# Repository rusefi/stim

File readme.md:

[Interactive Pinout](https://rusefi.com/docs/pinouts/stim/)

## User Manual

* 12v DC power required
* one microUSB cable required for operation
* sometimes second microUSB is useful for firmware update

* [Download Putty](https://www.chiark.greenend.org.uk/~sgtatham/putty/latest.html)
* bottom microUSB is required for operation
* top microUSB is sometimes needed for firmware updates
* blinking blue LD2 means "alive"
* red LD3 means "board has failed test
* green LD1 next to blinking blue means "test successful"

See https://github.com/rusefi/rusefi-hardware/tree/main/digital-inputs for firmware

Part of https://github.com/rusefi/rusefi infrastucture

https://github.com/rusefi/rusefi/wiki/dev-hardware-quality-control

# Digital Inputs
- 48 channels of high/low digital inputs
- pin requirment: 4 ADC inputs and 9 GPIO

GPIO:
* output: x4 address pins
* output: x4 test control pins
* output: mux off

See https://github.com/rusefi/stim/issues/6

# Changelog

## rev C

* CAN board fix
* second CAN board added
* OUT0 pin moved from PA11 to PD8
* https://github.com/rusefi/stim/issues?q=label%3Arev-C+is%3Aclosed

## rev 0.2

* CAN bus
* superseal header

##  rev 0.1
* it works!

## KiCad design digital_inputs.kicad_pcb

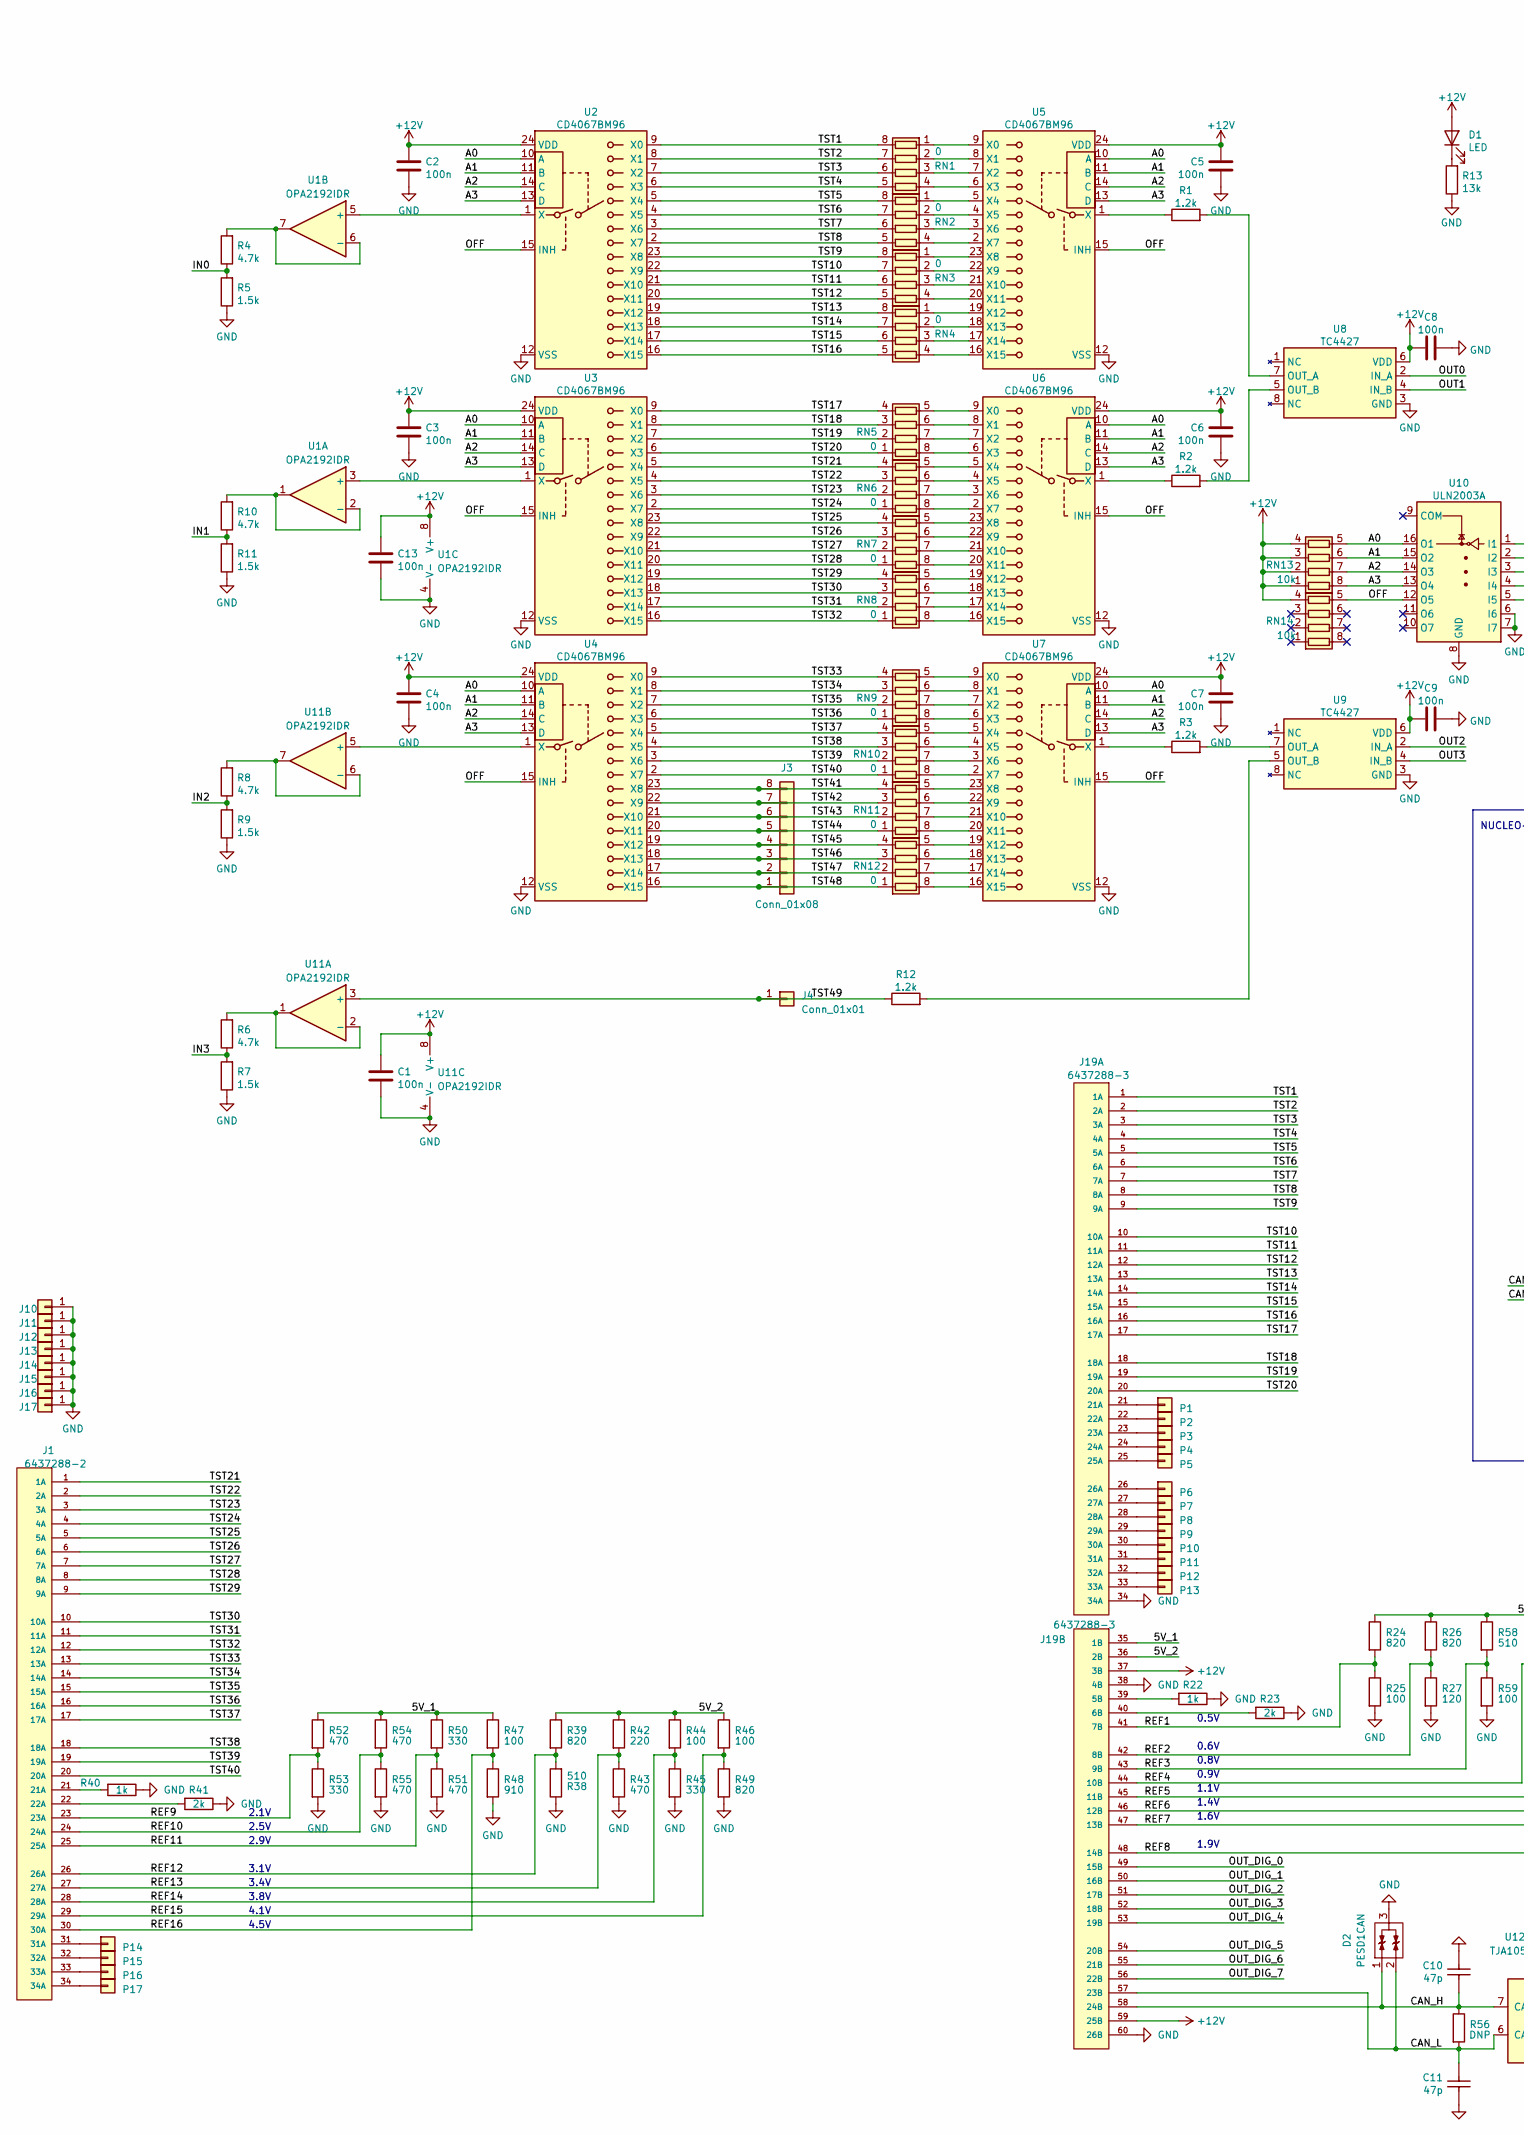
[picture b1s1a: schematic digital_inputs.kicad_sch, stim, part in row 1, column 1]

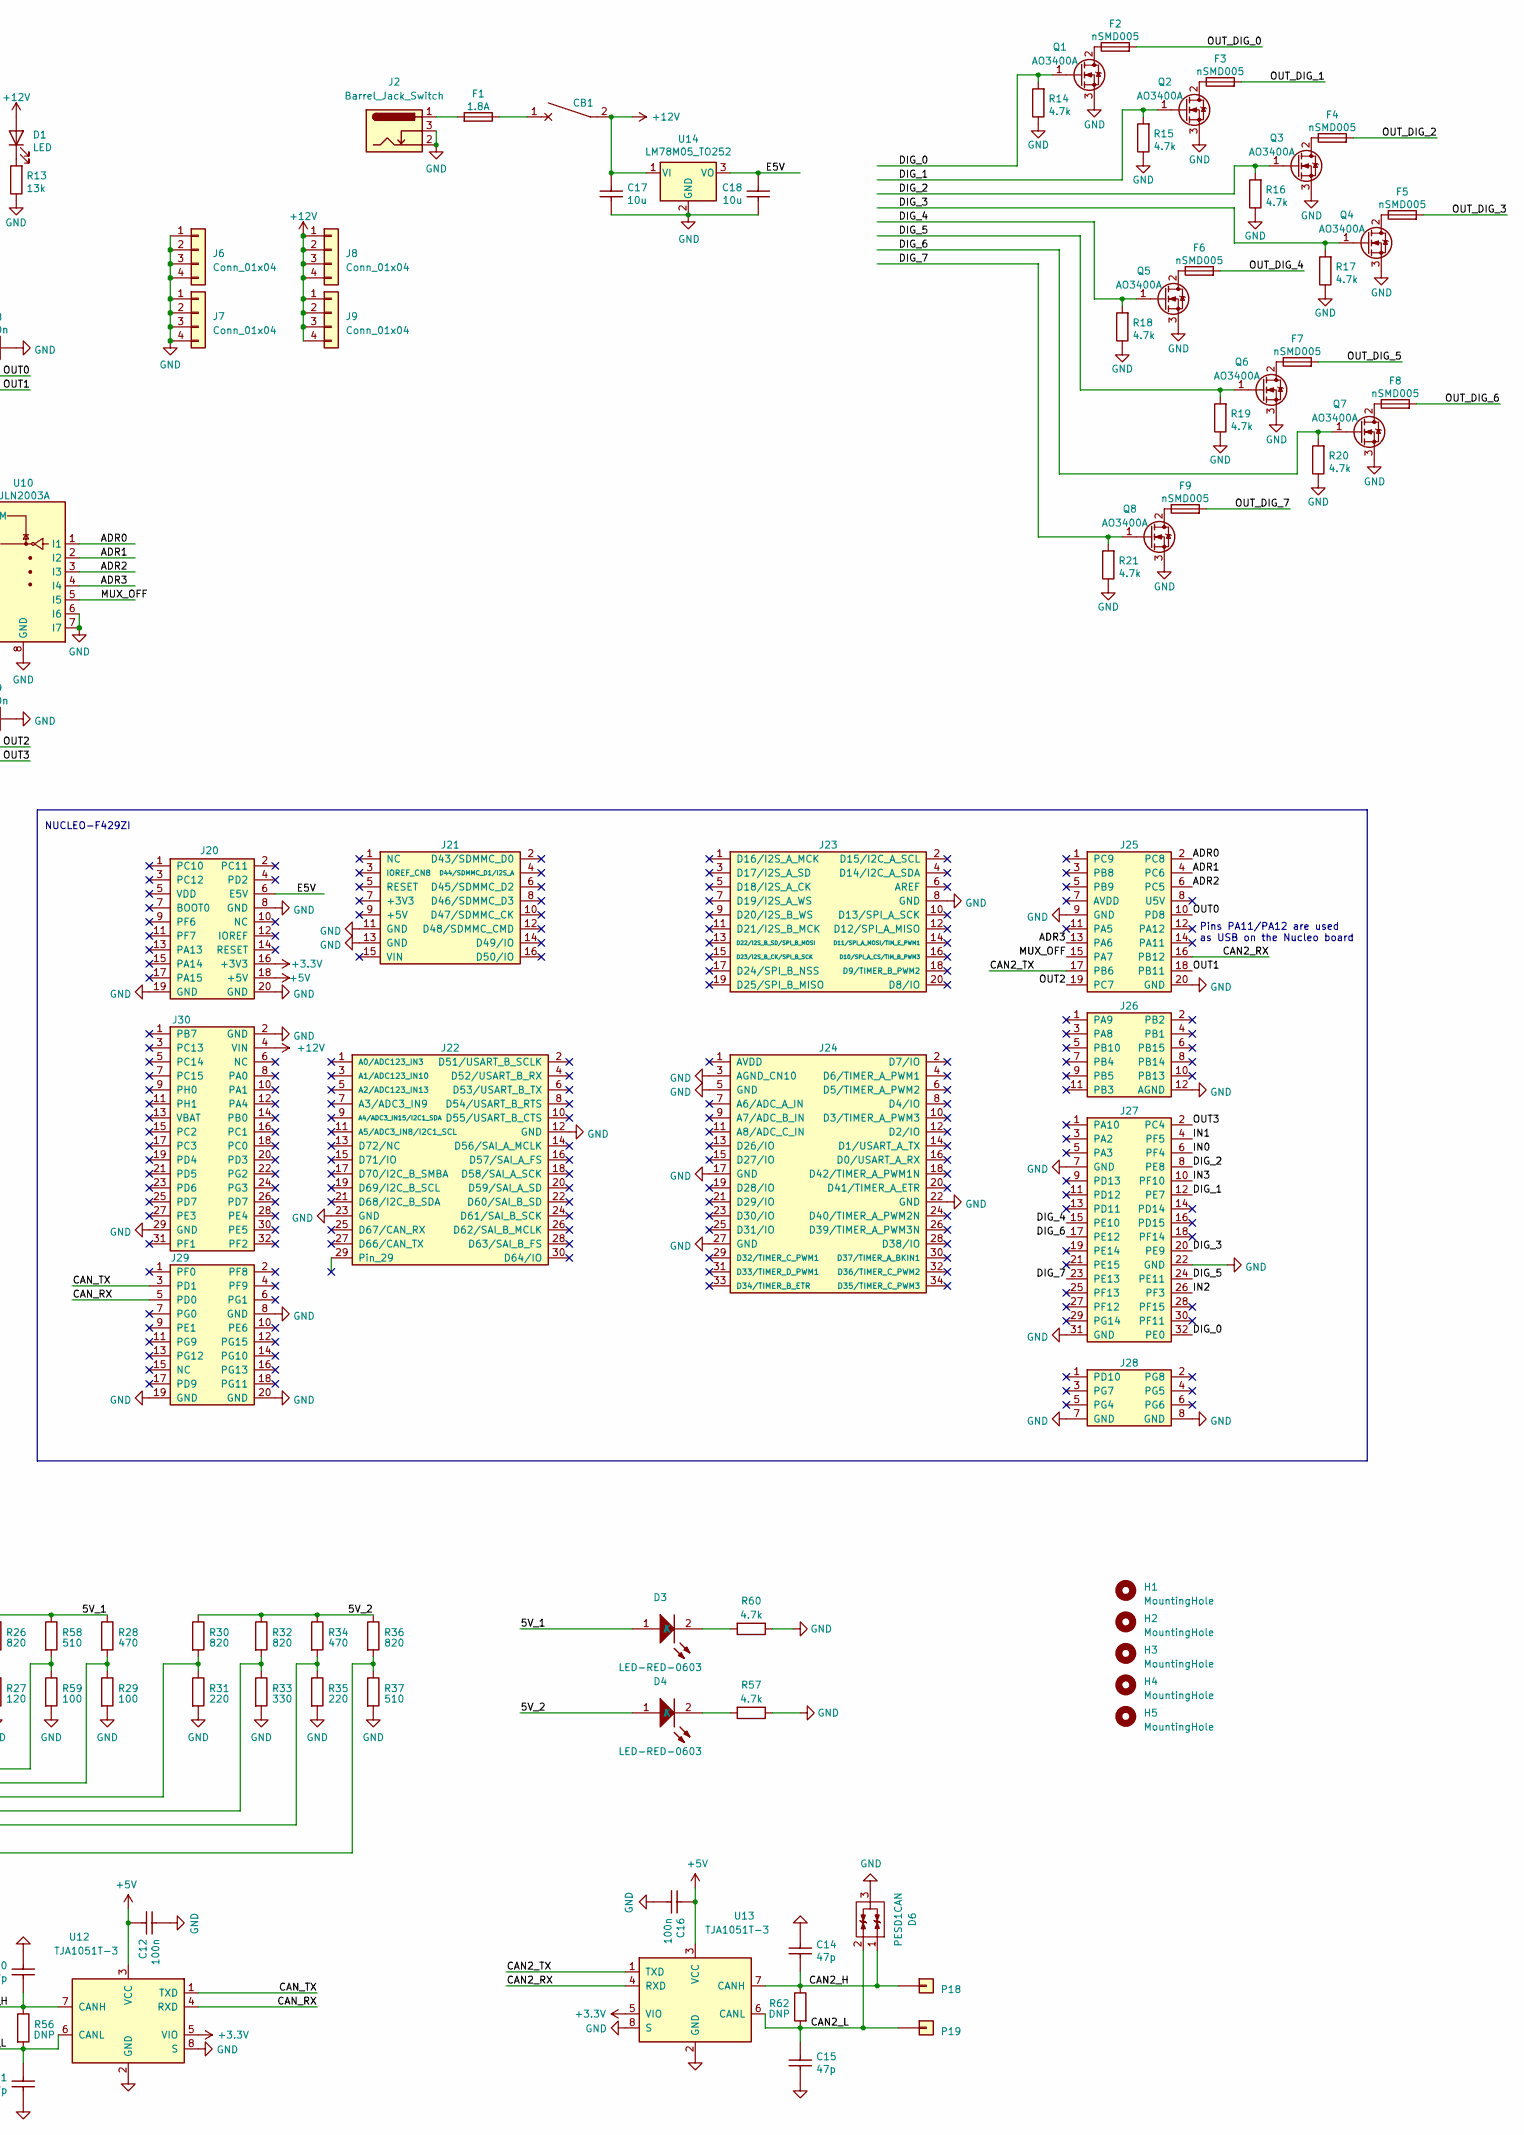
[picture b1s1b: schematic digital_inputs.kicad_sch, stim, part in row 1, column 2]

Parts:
C1, C2, C3, C4, C5, C6, C7, C8, C9, C12, C13, C16: 100n; C_0603_1608Metric; LCSC C14663
C10, C11, C14, C15: 47p; C_0603_1608Metric; LCSC C1671
C17, C18: 10u; C_0805_2012Metric; LCSC C15850
CB1: CircuitBreaker_1P; RS601HL-1010011BB; LCSC C2885782
D1: LED; LED_0805_2012Metric; LCSC C2297
D2, D6: PESD1CAN; SOT-23; LCSC C343993
D3, D4: LED-RED-0603; LED-0603; LCSC C2286
F1: 1.8A; Fuse_1206_3216Metric; LCSC C369161
F2, F3, F4, F5, F6, F7, F8, F9: nSMD005; Fuse_1206_3216Metric; LCSC C369153
H1, H2, H3, H4, H5: MountingHole; MountingHole_3.2mm_M3
J1: 6437288-2
J2: Barrel_Jack_Switch; BarrelJack_GCT_DCJ200-10-A_Horizontal; LCSC C111567
J3: Conn_01x08; TerminalBlock_Phoenix_MKDS-1,5-8-5.08_1x08_P5.08mm_Horizont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
J4: Conn_01x01; SolderWire-0.75sqmm_1x01_D1.25mm_OD2.3mm
J6, J7, J8, J9: Conn_01x04; TerminalBlock_Phoenix_MKDS-1,5-4-5.08_1x04_P5.08mm_Horizont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
J10, J11, J12, J13, J14, J15, J16, J17: Conn_01x01; MountingHole_3.2mm_M3_Pad_Via
J19: 6437288-3; TE_6437288-3; LCSC C591769
J20, J25, J29: Conn_02x10_Odd_Even; PinHeader_2x10_P2.54mm_Vertical; LCSC C92266
J21: Conn_02x08_Odd_Even; PinHeader_2x08_P2.54mm_Vertical
J22: Conn_02x15_Odd_Even; PinHeader_2x15_P2.54mm_Vertical
J23: Conn_02x10_Odd_Even; PinHeader_2x10_P2.54mm_Vertical
J24: Conn_02x17_Odd_Even; PinHeader_2x17_P2.54mm_Vertical
J26: Conn_02x06_Odd_Even; PinHeader_2x06_P2.54mm_Vertical
J27: Conn_02x16_Odd_Even; PinHeader_2x16_P2.54mm_Vertical; LCSC C132130
J28: Conn_02x04_Odd_Even; PinHeader_2x04_P2.54mm_Vertical
J30: Conn_02x14_Odd_Even; PinHeader_2x16_P2.54mm_Vertical
P1, P2, P3, P4, P5, P6, P7, P8, P9, P10, P11, P12, P13, P14, P15, P16, P17, P18, P19: Pad; PAD-TH
Q1, Q2, Q3, Q4, Q5, Q6, Q7, Q8: AO3400A; SOT-23; LCSC C20917
R1, R2, R3, R12: 1.2k; R_1206_3216Metric; LCSC C26035
R4, R6, R8, R10, R14, R15, R16, R17, R18, R19, R20, R21, R57, R60: 4.7k; R_0603_1608Metric; LCSC C23162
R5, R7, R9, R11: 1.5k; R_0603_1608Metric; LCSC C22843
R13: 13k; R_0603_1608Metric; LCSC C22797
R22, R40: 1k; R_0603_1608Metric; LCSC C21190
R23, R41: 2k; R_0603_1608Metric; LCSC C4190
R24, R26, R30, R32, R36, R39, R49: 820; R_0603_1608Metric; LCSC C23253
R25, R29, R44, R46, R47, R59: 100; R_0603_1608Metric; LCSC C22775
R27: 120; R_0603_1608Metric; LCSC C22787
R28, R34, R43, R51, R52, R54, R55: 470; R_0603_1608Metric; LCSC C23179
R31, R35, R42: 220; R_0603_1608Metric; LCSC C22962
R33, R45, R50, R53: 330; R_0603_1608Metric; LCSC C23138
R37, R38, R58: 510; R_0603_1608Metric; LCSC C23193
R48: 910; R_0603_1608Metric; LCSC C23264
R56, R62: DNP; R_0603_1608Metric
RN1, RN2, RN3, RN4, RN5, RN6, RN7, RN8, RN9, RN10, RN11, RN12: 0; R_Array_Convex_4x0603; LCSC C327053
RN13, RN14: 10k; R_Array_Convex_4x0603; LCSC C29718
U1, U11: OPA2192IDR; SO-8_3.9x4.9mm_P1.27mm; LCSC C110074
U2, U3, U4, U5, U6, U7: CD4067BM96; SOIC-24W_7.5x15.4mm_P1.27mm; LCSC C6525
U8, U9: TC4427; SOIC-8_3.9x4.9mm_P1.27mm; LCSC C20551
U10: ULN2003A; SOIC-16_3.9x9.9mm_P1.27mm; LCSC C7512
U12, U13: TJA1051T-3; SOIC-8_3.9x4.9mm_P1.27mm; LCSC C38695
U14: LM78M05_TO252; TO-252-2; LCSC C58069

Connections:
+3.3V: J20.16 (+3V3), U12.5 (VIO), U13.5 (VIO)
+5V: C12.2, C16.2, J20.18 (+5V), U12.3 (VCC), U13.3 (VCC)
+12V: C1.2, C2.2, C3.2, C4.2, C5.2, C6.2, C7.2, C8.1, C9.1, C13.2, C17.2, CB1.2, D1.2 (A), J8.1, J8.2, J8.3, J8.4, J9.1, J9.2, J9.3, J9.4, J19.37 (3B), J19.59 (25B), J30.4 (VIN), RN13.1 (R1.1), RN13.2 (R2.1), RN13.3 (R3.1), RN13.4 (R4.1), RN14.4 (R4.1), U1.8 (V+), U2.24 (VDD), U3.24 (VDD), U4.24 (VDD), U5.24 (VDD), U6.24 (VDD), U7.24 (VDD), U8.6 (VDD), U9.6 (VDD), U11.8 (V+), U14.1 (VI)
/5V_1: D3.1 (A), J19.35 (1B), R24.1, R26.1, R28.1, R47.1, R50.1, R52.1, R54.1, R58.1
/5V_2: D4.1 (A), J19.36 (2B), R30.1, R32.1, R34.1, R36.1, R39.1, R42.1, R44.1, R46.1
/A0: RN13.5 (R4.2), U2.10 (A), U3.10 (A), U4.10 (A), U5.10 (A), U6.10 (A), U7.10 (A), U10.16 (O1)
/A1: RN13.6 (R3.2), U2.11 (B), U3.11 (B), U4.11 (B), U5.11 (B), U6.11 (B), U7.11 (B), U10.15 (O2)
/A2: RN13.7 (R2.2), U2.14 (C), U3.14 (C), U4.14 (C), U5.14 (C), U6.14 (C), U7.14 (C), U10.14 (O3)
/A3: RN13.8 (R1.2), U2.13 (D), U3.13 (D), U4.13 (D), U5.13 (D), U6.13 (D), U7.13 (D), U10.13 (O4)
/ADR0: J25.2 (PC8), U10.1 (I1)
/ADR1: J25.4 (PC6), U10.2 (I2)
/ADR2: J25.6 (PC5), U10.3 (I3)
/ADR3: J25.13 (PA6), U10.4 (I4)
/CAN2_H: C14.1, D6.1 (G), P18.1, R62.1, U13.7 (CANH)
/CAN2_L: C15.2, D6.2 (D), P19.1, R62.2, U13.6 (CANL)
/CAN2_RX: J25.16 (PB12), U13.4 (RXD)
/CAN2_TX: J25.17 (PB6), U13.1 (TXD)
/CAN_H: C10.1, D2.1 (G), J19.58 (24B), R56.1, U12.7 (CANH)
/CAN_L: C11.2, D2.2 (D), J19.57 (23B), R56.2, U12.6 (CANL)
/CAN_RX: J29.5 (PD0), U12.4 (RXD)
/CAN_TX: J29.3 (PD1), U12.1 (TXD)
/DIG_0: J27.32 (PE0), Q1.1 (G), R14.2
/DIG_1: J27.12 (PE7), Q2.1 (G), R15.2
/DIG_2: J27.8 (PE8), Q3.1 (G), R16.2
/DIG_3: J27.20 (PE9), Q4.1 (G), R17.2
/DIG_4: J27.15 (PE10), Q5.1 (G), R18.2
/DIG_5: J27.24 (PE11), Q6.1 (G), R19.2
/DIG_6: J27.17 (PE12), Q7.1 (G), R20.2
/DIG_7: J27.23 (PE13), Q8.1 (G), R21.2
/E5V: C18.2, J20.6 (E5V), U14.3 (VO)
/IN0: J27.6 (PF4), R4.1, R5.2
/IN1: J27.4 (PF5), R10.1, R11.2
/IN2: J27.26 (PF3), R8.1, R9.2
/IN3: J27.10 (PF10), R6.1, R7.2
/MUX_OFF: J25.15 (PA7), U10.5 (I5)
/OFF: RN14.5 (R4.2), U2.15 (INH), U3.15 (INH), U4.15 (INH), U5.15 (INH), U6.15 (INH), U7.15 (INH), U10.12 (O5)
/OUT0: J25.10 (PD8), U8.2 (IN_A)
/OUT1: J25.18 (PB11), U8.4 (IN_B)
/OUT2: J25.19 (PC7), U9.2 (IN_A)
/OUT3: J27.2 (PC4), U9.4 (IN_B)
/OUT_DIG_0: F2.2, J19.49 (15B)
/OUT_DIG_1: F3.2, J19.50 (16B)
/OUT_DIG_2: F4.2, J19.51 (17B)
/OUT_DIG_3: F5.2, J19.52 (18B)
/OUT_DIG_4: F6.2, J19.53 (19B)
/OUT_DIG_5: F7.2, J19.54 (20B)
/OUT_DIG_6: F8.2, J19.55 (21B)
/OUT_DIG_7: F9.2, J19.56 (22B)
/REF1: J19.41 (7B), R24.2, R25.1
/REF2: J19.42 (8B), R26.2, R27.1
/REF3: J19.43 (9B), R58.2, R59.1
/REF4: J19.44 (10B), R28.2, R29.1
/REF5: J19.45 (11B), R30.2, R31.1
/REF6: J19.46 (12B), R32.2, R33.1
/REF7: J19.47 (13B), R34.2, R35.1
/REF8: J19.48 (14B), R36.2, R37.1
/REF9: J1.23 (23A), R52.2, R53.1
/REF10: J1.24 (24A), R54.2, R55.1
/REF11: J1.25 (25A), R50.2, R51.1
/REF12: J1.26 (26A), R38.2, R39.2
/REF13: J1.27 (27A), R42.2, R43.1
/REF14: J1.28 (28A), R44.2, R45.1
/REF15: J1.29 (29A), R46.2, R49.1
/REF16: J1.30 (30A), R47.2, R48.1
/TST1: J19.1 (1A), RN1.8 (R1.2), U2.9 (X0)
/TST2: J19.2 (2A), RN1.7 (R2.2), U2.8 (X1)
/TST3: J19.3 (3A), RN1.6 (R3.2), U2.7 (X2)
/TST4: J19.4 (4A), RN1.5 (R4.2), U2.6 (X3)
/TST5: J19.5 (5A), RN2.8 (R1.2), U2.5 (X4)
/TST6: J19.6 (6A), RN2.7 (R2.2), U2.4 (X5)
/TST7: J19.7 (7A), RN2.6 (R3.2), U2.3 (X6)
/TST8: J19.8 (8A), RN2.5 (R4.2), U2.2 (X7)
/TST9: J19.9 (9A), RN3.8 (R1.2), U2.23 (X8)
/TST10: J19.10 (10A), RN3.7 (R2.2), U2.22 (X9)
/TST11: J19.11 (11A), RN3.6 (R3.2), U2.21 (X10)
/TST12: J19.12 (12A), RN3.5 (R4.2), U2.20 (X11)
/TST13: J19.13 (13A), RN4.8 (R1.2), U2.19 (X12)
/TST14: J19.14 (14A), RN4.7 (R2.2), U2.18 (X13)
/TST15: J19.15 (15A), RN4.6 (R3.2), U2.17 (X14)
/TST16: J19.16 (16A), RN4.5 (R4.2), U2.16 (X15)
/TST17: J19.17 (17A), RN5.4 (R4.1), U3.9 (X0)
/TST18: J19.18 (18A), RN5.3 (R3.1), U3.8 (X1)
/TST19: J19.19 (19A), RN5.2 (R2.1), U3.7 (X2)
/TST20: J19.20 (20A), RN5.1 (R1.1), U3.6 (X3)
/TST21: J1.1 (1A), RN6.4 (R4.1), U3.5 (X4)
/TST22: J1.2 (2A), RN6.3 (R3.1), U3.4 (X5)
/TST23: J1.3 (3A), RN6.2 (R2.1), U3.3 (X6)
/TST24: J1.4 (4A), RN6.1 (R1.1), U3.2 (X7)
/TST25: J1.5 (5A), RN7.4 (R4.1), U3.23 (X8)
/TST26: J1.6 (6A), RN7.3 (R3.1), U3.22 (X9)
/TST27: J1.7 (7A), RN7.2 (R2.1), U3.21 (X10)
/TST28: J1.8 (8A), RN7.1 (R1.1), U3.20 (X11)
/TST29: J1.9 (9A), RN8.4 (R4.1), U3.19 (X12)
/TST30: J1.10 (10A), RN8.3 (R3.1), U3.18 (X13)
/TST31: J1.11 (11A), RN8.2 (R2.1), U3.17 (X14)
/TST32: J1.12 (12A), RN8.1 (R1.1), U3.16 (X15)
/TST33: J1.13 (13A), RN9.4 (R4.1), U4.9 (X0)
/TST34: J1.14 (14A), RN9.3 (R3.1), U4.8 (X1)
/TST35: J1.15 (15A), RN9.2 (R2.1), U4.7 (X2)
/TST36: J1.16 (16A), RN9.1 (R1.1), U4.6 (X3)
/TST37: J1.17 (17A), RN10.4 (R4.1), U4.5 (X4)
/TST38: J1.18 (18A), RN10.3 (R3.1), U4.4 (X5)
/TST39: J1.19 (19A), RN10.2 (R2.1), U4.3 (X6)
/TST40: J1.20 (20A), RN10.1 (R1.1), U4.2 (X7)
/TST41: J3.8, RN11.4 (R4.1), U4.23 (X8)
/TST42: J3.7, RN11.3 (R3.1), U4.22 (X9)
/TST43: J3.6, RN11.2 (R2.1), U4.21 (X10)
/TST44: J3.5, RN11.1 (R1.1), U4.20 (X11)
/TST45: J3.4, RN12.4 (R4.1), U4.19 (X12)
/TST46: J3.3, RN12.3 (R3.1), U4.18 (X13)
/TST47: J3.2, RN12.2 (R2.1), U4.17 (X14)
/TST48: J3.1, RN12.1 (R1.1), U4.16 (X15)
/TST49: J4.1, R12.1, U11.3 (+)
GND: C1.1, C2.1, C3.1, C4.1, C5.1, C6.1, C7.1, C8.2, C9.2, C10.2, C11.1, C12.1, C13.1, C14.2, C15.1, C16.1, C17.1, C18.1, D2.3 (S), D6.3 (S), J2.2, J2.3, J6.1, J6.2, J6.3, J6.4, J7.1, J7.2, J7.3, J7.4, J10.1, J11.1, J12.1, J13.1, J14.1, J15.1, J16.1, J17.1, J19.34 (34A), J19.38 (4B), J19.60 (26B), J20.8 (GND), J20.19 (GND), J20.20 (GND), J21.11 (GND), J21.13 (GND), J22.12 (GND), J22.23 (GND), J23.8 (GND), J24.3 (AGND_CN10), J24.5 (GND), J24.17 (GND), J24.22 (GND), J24.27 (GND), J25.9 (GND), J25.20 (GND), J26.12 (AGND), J27.7 (GND), J27.22 (GND), J27.31 (GND), J28.7 (GND), J28.8 (GND), J29.8 (GND), J29.19 (GND), J29.20 (GND), J30.2 (GND), J30.29 (GND), Q1.3 (S), Q2.3 (S), Q3.3 (S), Q4.3 (S), Q5.3 (S), Q6.3 (S), Q7.3 (S), Q8.3 (S), R5.1, R7.1, R9.1, R11.1, R13.1, R14.1, R15.1, R16.1, R17.1, R18.1, R19.1, R20.1, R21.1, R22.1, R23.1, R25.2, R27.2, R29.2, R31.2, R33.2, R35.2, R37.2, R38.1, R40.1, R41.1, R43.2, R45.2, R48.2, R49.2, R51.2, R53.2, R55.2, R57.1, R59.2, R60.1, U1.4 (V-), U2.12 (VSS), U3.12 (VSS), U4.12 (VSS), U5.12 (VSS), U6.12 (VSS), U7.12 (VSS), U8.3 (GND), U9.3 (GND), U10.6 (I6), U10.7 (I7), U10.8 (GND), U11.4 (V-), U12.2 (GND), U12.8 (S), U13.2 (GND), U13.8 (S), U14.2 (GND)
unnamed: CB1.1, F1.1
unnamed: D1.1 (K), R13.2
unnamed: D3.2 (K), R60.2
unnamed: D4.2 (K), R57.2
unnamed: F1.2, J2.1
unnamed: J1.21 (21A), R40.2
unnamed: J1.22 (22A), R41.2
unnamed: J1.31 (31A), P14.1
unnamed: J1.32 (32A), P15.1
unnamed: J1.33 (33A), P16.1
unnamed: J1.34 (34A), P17.1
unnamed: J19.21 (21A), P1.1
unnamed: J19.22 (22A), P2.1
unnamed: J19.23 (23A), P3.1
unnamed: J19.24 (24A), P4.1
unnamed: J19.25 (25A), P5.1
unnamed: J19.26 (26A), P6.1
unnamed: J19.27 (27A), P7.1
unnamed: J19.28 (28A), P8.1
unnamed: J19.29 (29A), P9.1
unnamed: J19.30 (30A), P10.1
unnamed: J19.31 (31A), P11.1
unnamed: J19.32 (32A), P12.1
unnamed: J19.33 (33A), P13.1
unnamed: J19.39 (5B), R22.2
unnamed: J19.40 (6B), R23.2
unnamed: F2.1, Q1.2 (D)
unnamed: F3.1, Q2.2 (D)
unnamed: F4.1, Q3.2 (D)
unnamed: F5.1, Q4.2 (D)
unnamed: F6.1, Q5.2 (D)
unnamed: F7.1, Q6.2 (D)
unnamed: F8.1, Q7.2 (D)
unnamed: F9.1, Q8.2 (D)
unnamed: RN1.1 (R1.1), U5.9 (X0)
unnamed: RN1.2 (R2.1), U5.8 (X1)
unnamed: RN1.3 (R3.1), U5.7 (X2)
unnamed: RN1.4 (R4.1), U5.6 (X3)
unnamed: RN2.1 (R1.1), U5.5 (X4)
unnamed: RN2.2 (R2.1), U5.4 (X5)
unnamed: RN2.3 (R3.1), U5.3 (X6)
unnamed: RN2.4 (R4.1), U5.2 (X7)
unnamed: RN3.1 (R1.1), U5.23 (X8)
unnamed: RN3.2 (R2.1), U5.22 (X9)
unnamed: RN3.3 (R3.1), U5.21 (X10)
unnamed: RN3.4 (R4.1), U5.20 (X11)
unnamed: RN4.1 (R1.1), U5.19 (X12)
unnamed: RN4.2 (R2.1), U5.18 (X13)
unnamed: RN4.3 (R3.1), U5.17 (X14)
unnamed: RN4.4 (R4.1), U5.16 (X15)
unnamed: RN5.8 (R1.2), U6.6 (X3)
unnamed: RN5.7 (R2.2), U6.7 (X2)
unnamed: RN5.6 (R3.2), U6.8 (X1)
unnamed: RN5.5 (R4.2), U6.9 (X0)
unnamed: RN6.8 (R1.2), U6.2 (X7)
unnamed: RN6.7 (R2.2), U6.3 (X6)
unnamed: RN6.6 (R3.2), U6.4 (X5)
unnamed: RN6.5 (R4.2), U6.5 (X4)
unnamed: RN7.8 (R1.2), U6.20 (X11)
unnamed: RN7.7 (R2.2), U6.21 (X10)
unnamed: RN7.6 (R3.2), U6.22 (X9)
unnamed: RN7.5 (R4.2), U6.23 (X8)
unnamed: RN8.8 (R1.2), U6.16 (X15)
unnamed: RN8.7 (R2.2), U6.17 (X14)
unnamed: RN8.6 (R3.2), U6.18 (X13)
unnamed: RN8.5 (R4.2), U6.19 (X12)
unnamed: RN9.8 (R1.2), U7.6 (X3)
unnamed: RN9.7 (R2.2), U7.7 (X2)
unnamed: RN9.6 (R3.2), U7.8 (X1)
unnamed: RN9.5 (R4.2), U7.9 (X0)
unnamed: RN10.8 (R1.2), U7.2 (X7)
unnamed: RN10.7 (R2.2), U7.3 (X6)
unnamed: RN10.6 (R3.2), U7.4 (X5)
unnamed: RN10.5 (R4.2), U7.5 (X4)
unnamed: RN11.8 (R1.2), U7.20 (X11)
unnamed: RN11.7 (R2.2), U7.21 (X10)
unnamed: RN11.6 (R3.2), U7.22 (X9)
unnamed: RN11.5 (R4.2), U7.23 (X8)
unnamed: RN12.8 (R1.2), U7.16 (X15)
unnamed: RN12.7 (R2.2), U7.17 (X14)
unnamed: RN12.6 (R3.2), U7.18 (X13)
unnamed: RN12.5 (R4.2), U7.19 (X12)
unnamed: U1.3 (+), U3.1 (X)
unnamed: R10.2, U1.1, U1.2 (-)
unnamed: U1.5 (+), U2.1 (X)
unnamed: R4.2, U1.6 (-), U1.7
unnamed: R1.1, U5.1 (X)
unnamed: R2.1, U6.1 (X)
unnamed: R3.1, U7.1 (X)
unnamed: R1.2, U8.7 (OUT_A)
unnamed: R2.2, U8.5 (OUT_B)
unnamed: R3.2, U9.7 (OUT_A)
unnamed: R12.2, U9.5 (OUT_B)
unnamed: R6.2, U11.1, U11.2 (-)
unnamed: U4.1 (X), U11.5 (+)
unnamed: R8.2, U11.6 (-), U11.7

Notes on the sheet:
1.4V
3.8V
1.1V
Pins PA11/PA12 are used as USB on the Nucleo board
0.9V
1.6V
4.5V
3.4V
NUCLEO-F429ZI
0.5V
1.9V
0.8V
3.1V
2.1V
2.5V
0.6V
4.1V
2.9V

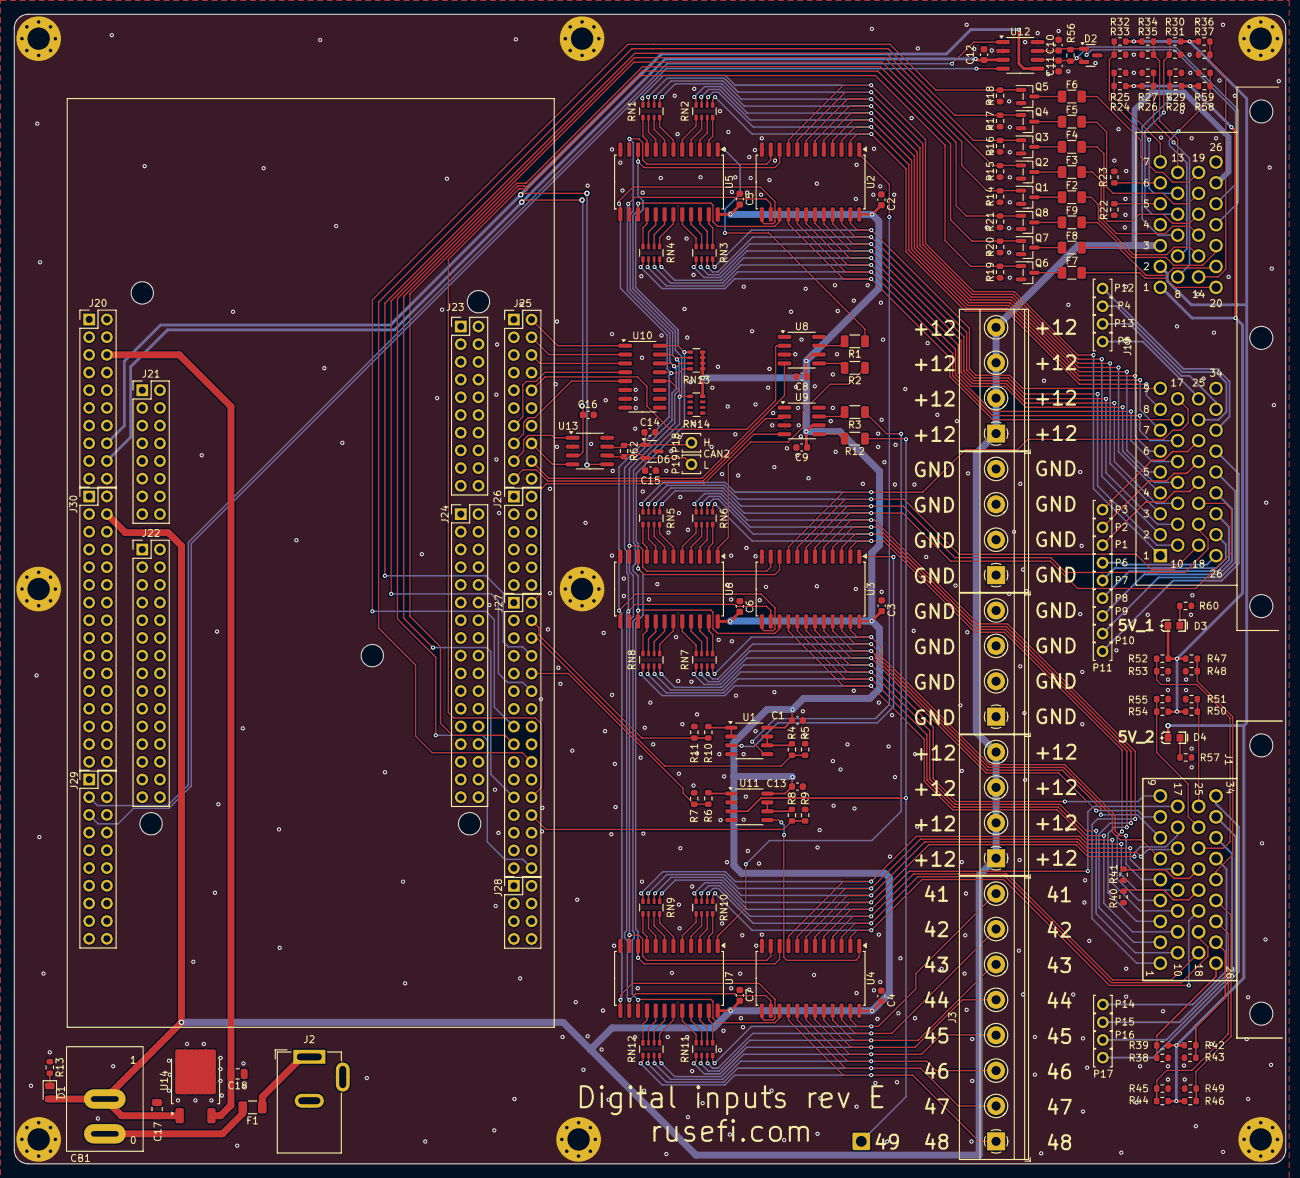
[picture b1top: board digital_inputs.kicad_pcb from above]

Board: 2 copper layers, 182.5 x 165.0 mm, 182 parts (0 on the bottom side), 210 nets.

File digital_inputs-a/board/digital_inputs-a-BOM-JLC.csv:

Comment,Designator,Footprint,LCSC Part #
"100n","C1, C2, C3, C4, C5, C6, C7, C8, C9, C12, C13","C0603","C14663"
"47p","C10, C11","C0603","C1671"
"LED","D1","LED_0805_2012Metric","C2297"
"PESD1CAN","D2","SOT-23","C343993"
"1.8A","F1","Fuse_1206_3216Metric","C369161"
"Conn_02x05_Odd_Even","J18","PinHeader_2x05_P2.54mm_Vertical","C92270"
"Conn_02x10_Odd_Even","J25","PinHeader_2x10_P2.54mm_Vertical","C92266"
"Conn_02x16_Odd_Even","J27","PinHeader_2x16_P2.54mm_Vertical","C132130"
"AO3400A","Q1, Q2, Q3, Q4, Q5, Q6, Q7, Q8","SOT-23","C20917"
"1.2k","R1, R2, R3, R12","R1206","C26035"
"4.7k","R4, R6, R8, R10, R13, R14, R15, R16, R17, R18, R19, R20, R21","R0603","C23162"
"1.5k","R5, R7, R9, R11","R0603","C22843"
"1k","R22, R40","R0603","C21190"
"2k","R23, R41","R0603","C4190"
"820","R24, R26, R30, R32, R36, R39, R49","R0603","C23253"
"100","R25, R29, R44, R46, R47, R59","R0603","C22775"
"120","R27","R0603","C22787"
"470","R28, R34, R43, R51, R52, R54, R55","R0603","C23179"
"220","R31, R35, R42","R0603","C22962"
"330","R33, R45, R50, R53","R0603","C23138"
"510","R37, R38, R58","R0603","C23193"
"910","R48","R0603","C23264"
"0","RN1, RN2, RN3, RN4, RN5, RN6, RN7, RN8, RN9, RN10, RN11, RN12","R_Array_Convex_4x0603","C327053"
"10k","RN13, RN14","R_Array_Convex_4x0603","C29718"
"OPA2192IDR","U1, U11","SO-8_3.9x4.9mm_P1.27mm","C110074"
"CD4067BM96","U2, U3, U4, U5, U6, U7","SOIC-24W_7.5x15.4mm_P1.27mm","C6525"
"TC4427","U8, U9","SO8","C20551"
"ULN2003A","U10","SOIC-16_3.9x9.9mm_P1.27mm","C7512"
"TJA1051T-3","U12","SO8","C38695"
"nSMD005","F2, F3, F4, F5, F6, F7, F8, F9","F1206","C70064"

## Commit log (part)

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2021-07-19 Upd sch
2021-07-24 Upd sch & pcb
2021-07-25 Rename #8
2021-07-28 Fab preview
2021-07-28 fabbed!
2022-01-27 docs
2022-10-03 CAN power
2023-05-02 #14 #15
2023-07-22 pinout!
2023-07-27 add lib
2023-07-27 #3 #14 #16 #11 #17
2023-07-27 https://github.com/rusefi/stim/issues/17
2023-07-27 https://github.com/rusefi/stim/issues/16
2023-07-28 #16 #17
2023-08-01 Трассированная плата + файл замены U11
2023-08-02 hellen
2023-08-02 automation
2023-08-02 [skip actions] Auto-generated board
2023-08-02 more automation
2023-08-02 Upd pcb
2023-08-02 #14 #16 #23
2023-08-02 Fix empty board suffix https://github.com/andreika-git/hellen-one/issues/318
2023-08-08 check
2023-08-08 only basic processing for a moment
2023-08-08 re-enabling automation
2023-08-08 more proper approach to fp-info-cache
2023-08-08 Drill fix
2023-08-08 Remove boards
2023-08-08 Remove old gerbers
2023-08-08 Run create-board
2023-08-09 JLCPCB Part #
2023-08-09 JLC shortage fix
2023-08-10 Replace opamp
2023-08-13 0.2 is "rev a" fab
2023-08-20 CAN colors
2023-08-21 "rev C" #32
2023-08-21 #31 #26 #32 #33 #30
2023-08-21 bom_replace_digital_inputs-c
2023-08-21 yaml: give human names for some common analog outputs
2023-09-05 1-4 channels
2023-09-29 voltages
2023-10-30 #29 #39 #40
2023-11-07 2.10
2023-11-07 migrating mapping-path
2023-11-07 migrating mapping-path?
2023-11-07 https://github.com/chuckwagoncomputing/interactive-pinout/issues/14
2023-12-21 pinout progress
2024-01-04 Fix #41
2024-01-04 [skip actions] Auto-generated board v2.1
2024-01-05 Fix #42
2024-03-12 test num_layers=2 on stim https://github.com/andreika-git/hellen-one/issues/322
2024-05-01 TPS/PPS colors
2024-10-18 rev C changelog #43
2024-10-19 Rev D export
2024-10-19 adding more of modern automation
2024-10-19 reusing shared automation
2024-10-19 GHA says update hellen-one
2024-10-19 readme merge
2024-10-19 moving everything
2024-10-19 old and dead
2024-10-19 moving archive
2024-10-26 interactive-pinout@2.15
2025-01-19 enclosure
2025-02-14 poke
2025-04-13 new version
2025-04-13 ground
